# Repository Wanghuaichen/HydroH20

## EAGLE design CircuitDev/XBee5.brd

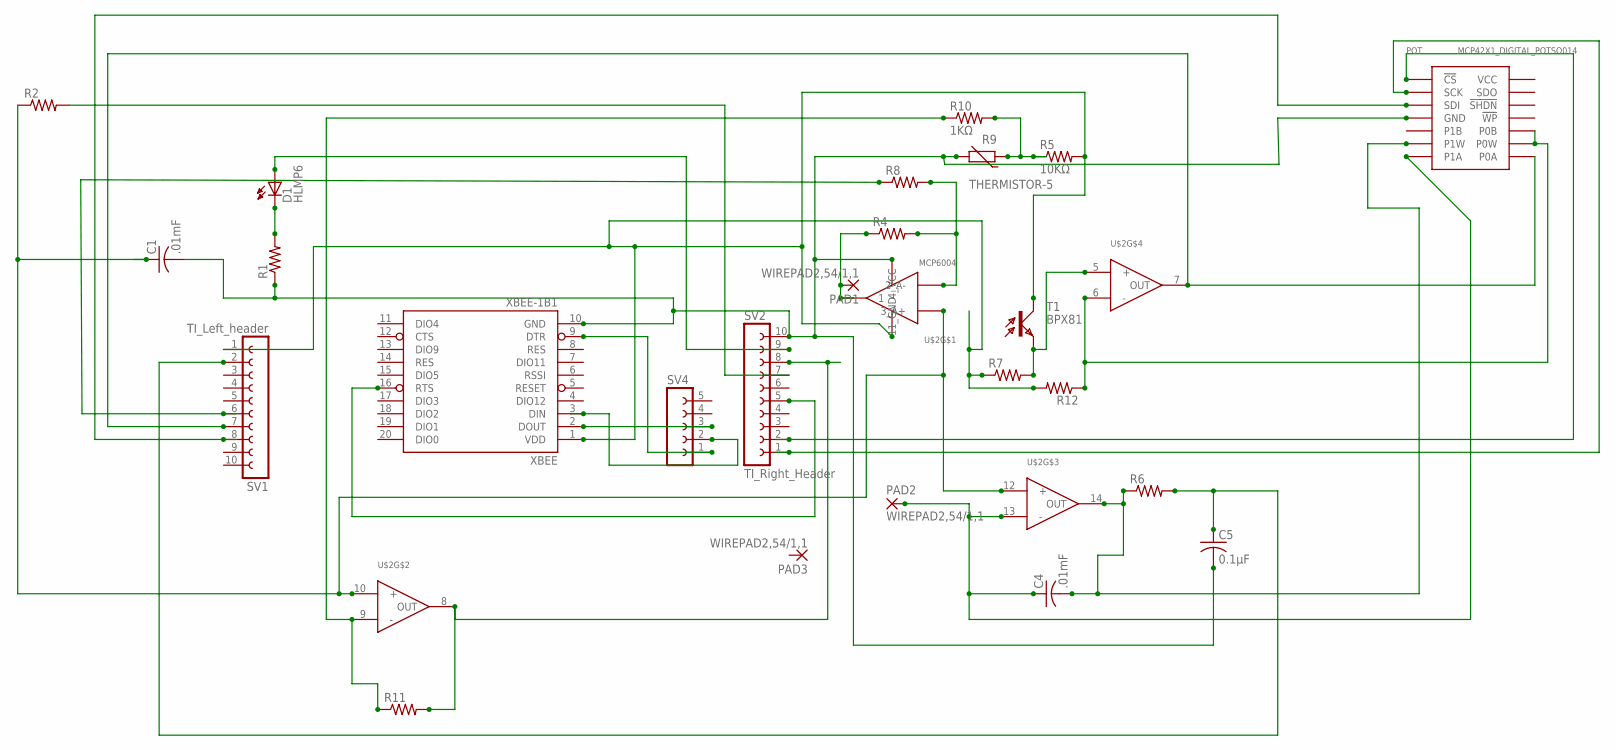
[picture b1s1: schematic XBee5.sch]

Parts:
C1, C4: .01mF; C0603
C5: 0.1μF; C0603
D1: HLMP6
PAD1, PAD2, PAD3: WIREPAD2,54/1,1; 2,54/1,1
POT: MCP42X1_DIGITAL_POTSO014; SO014
R1, R2, R4, R6, R7, R8, R11, R12: R-US_R0603; R0603
R5: 10KΩ; R0603
R9: THERMISTOR-5; R-5
R10: 1KΩ; R0603
SV1: TI_Left_header; FE10
SV2: TI_Right_Header; FE10
SV4: FE05-1
T1: BPX81
U$2: MCP6004; SO014
XBEE: XBEE-1B1; XBEE-1

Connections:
GND: C1.2, C5.2, POT.P4 (GND), R1.1, R9.2, SV2.10, U$2.11 (11_GND), XBEE.10 (GND)
unnamed: D1.K, R1.2
unnamed: R7.2, T1.E, U$2.5 (+)
unnamed: SV4.3, XBEE.2 (DOUT)
unnamed: SV4.1, XBEE.9 (DTR)
unnamed: SV4.2, XBEE.3 (DIN)
unnamed: R2.2, SV2.7
unnamed: POT.P9 (P0W), POT.P10 (P0B), R12.1, U$2.6 (-)
unnamed: R11.2, SV2.8, U$2.8 (OUT)
unnamed: R10.1, R11.1, U$2.9 (-)
unnamed: PAD1.1, R4.1, U$2.1
unnamed: D1.A, SV2.9
unnamed: C4.1, PAD2.1, POT.P7 (P1A), U$2.13 (-)
unnamed: C4.2, POT.P6 (P1W), R6.1, U$2.14 (OUT)
unnamed: C5.1, R6.2, SV1.2
unnamed: R5.1, R9.1, R10.2
unnamed: R4.2, R8.2, U$2.2 (2_A-)
unnamed: SV2.5, XBEE.16 (RTS)
POT_CS: POT.P1 (!CS), SV2.2
POT_SCK: POT.P2 (SCK), SV2.1
POT_SDI: POT.P3 (SDI), SV1.8
PULSE: R8.1, SV1.6
PWM-VCC/2: C1.1, R2.1, U$2.3 (3_A+), U$2.10 (+), U$2.12 (+)
TI_PN7_READ: POT.P8 (P0A), SV1.7, U$2.7 (OUT)
VCC: R5.2, R7.1, R12.2, SV1.1, T1.C, U$2.4 (4_VCC), XBEE.1 (VDD)

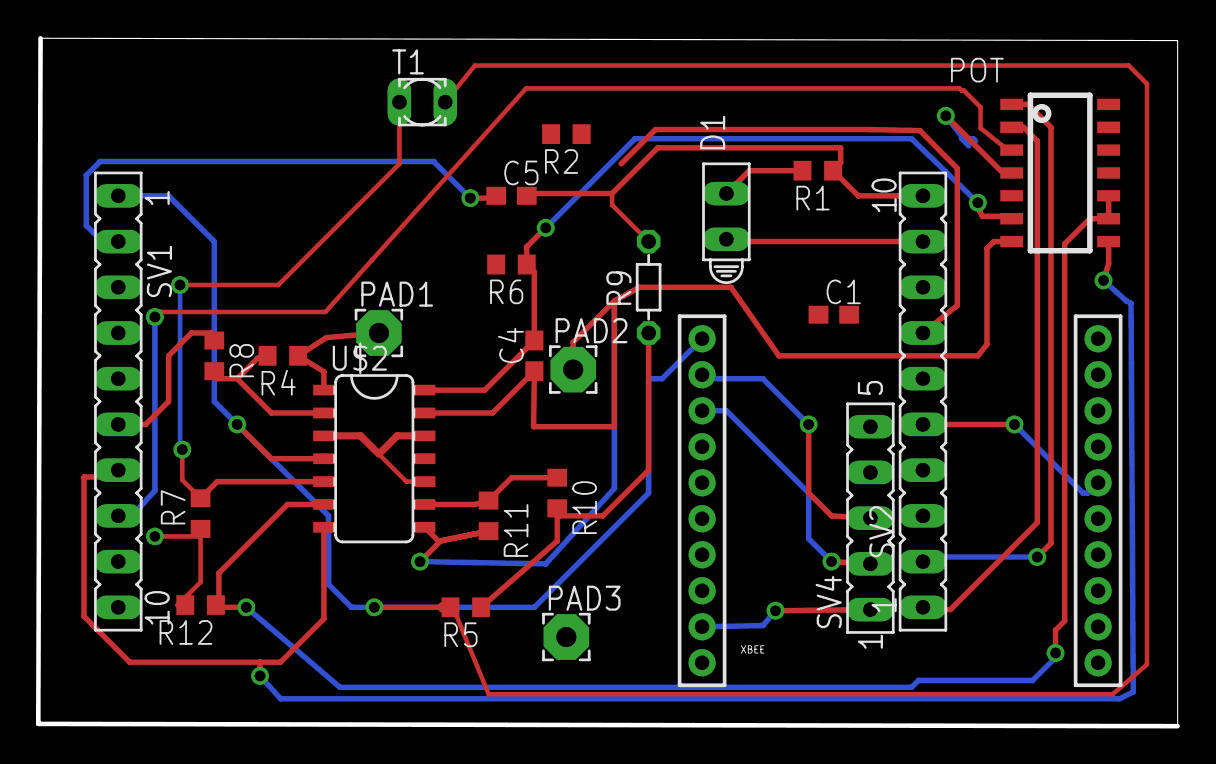
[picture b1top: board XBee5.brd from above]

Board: 2 copper layers, 63.3 x 38.2 mm, 25 parts (0 on the bottom side), 25 nets.

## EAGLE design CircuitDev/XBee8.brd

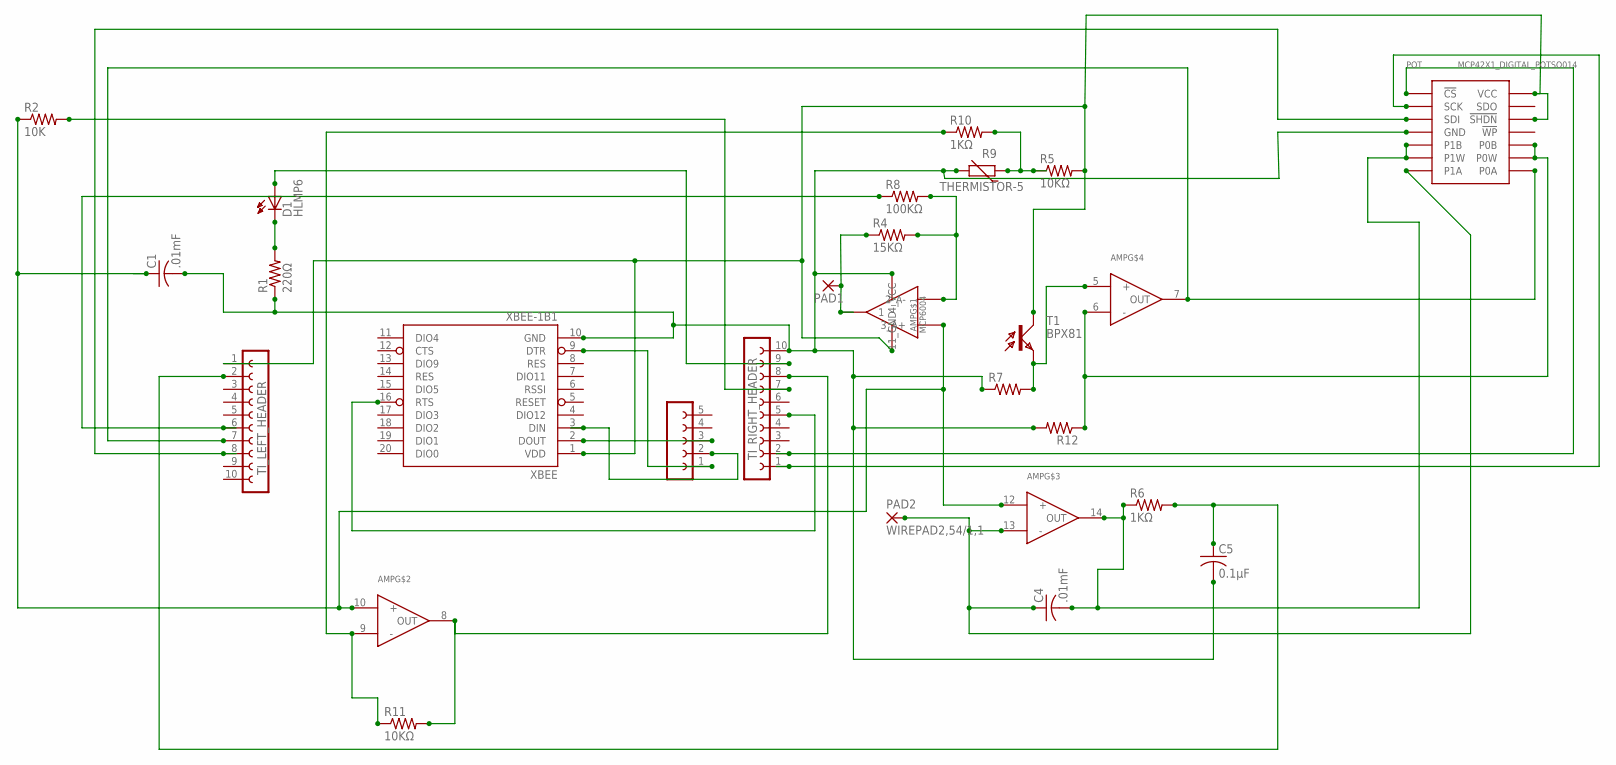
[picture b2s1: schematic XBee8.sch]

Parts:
AMP: MCP6004; SO014
C1, C4: .01mF; C0603
C5: 0.1μF; C0603
D1: HLMP6
PAD1, PAD2: WIREPAD2,54/1,1; 2,54/1,1
POT: MCP42X1_DIGITAL_POTSO014; SO014
R1: 220Ω; R0603
R2: 10K; R0603
R4: 15KΩ; R0603
R5, R11: 10KΩ; R0603
R6, R10: 1KΩ; R0603
R7, R12: R-US_R0603; R0603
R8: 100KΩ; R0603
R9: THERMISTOR-5; R-5
T1: BPX81
TI_LEFT_HEADER: FE10
TI_RIGHT_HEADER: FE10
XBEE: XBEE-1B1; XBEE-1
 : FE05-1

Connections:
GND: AMP.11 (11_GND), C1.2, C5.2, POT.P4 (GND), R1.1, R7.1, R9.2, R12.2, TI_RIGHT_HEADER.10, XBEE.10 (GND)
unnamed: D1.K, R1.2
unnamed: AMP.5 (+), R7.2, T1.E
unnamed: XBEE.2 (DOUT), .3
unnamed: XBEE.9 (DTR), .1
unnamed: XBEE.3 (DIN), .2
unnamed: R2.2, TI_RIGHT_HEADER.7
unnamed: AMP.6 (-), POT.P9 (P0W), POT.P10 (P0B), R12.1
unnamed: AMP.8 (OUT), R11.2, TI_RIGHT_HEADER.8
unnamed: AMP.9 (-), R10.1, R11.1
unnamed: AMP.1, PAD1.1, R4.1
unnamed: D1.A, TI_RIGHT_HEADER.9
unnamed: AMP.13 (-), C4.1, PAD2.1, POT.P7 (P1A)
unnamed: AMP.14 (OUT), C4.2, POT.P5 (P1B), POT.P6 (P1W), R6.1
unnamed: C5.1, R6.2, TI_LEFT_HEADER.2
unnamed: R5.1, R9.1, R10.2
unnamed: AMP.2 (2_A-), R4.2, R8.2
unnamed: TI_RIGHT_HEADER.5, XBEE.16 (RTS)
POT_CS: POT.P1 (!CS), TI_RIGHT_HEADER.2
POT_SCK: POT.P2 (SCK), TI_RIGHT_HEADER.1
POT_SDI: POT.P3 (SDI), TI_LEFT_HEADER.8
PULSE: R8.1, TI_LEFT_HEADER.6
PWM-VCC/2: AMP.3 (3_A+), AMP.10 (+), AMP.12 (+), C1.1, R2.1
TI_PN7_READ: AMP.7 (OUT), POT.P8 (P0A), TI_LEFT_HEADER.7
VCC: AMP.4 (4_VCC), POT.P12 (!SHDN), POT.P14 (VCC), R5.2, T1.C, TI_LEFT_HEADER.1, XBEE.1 (VDD)

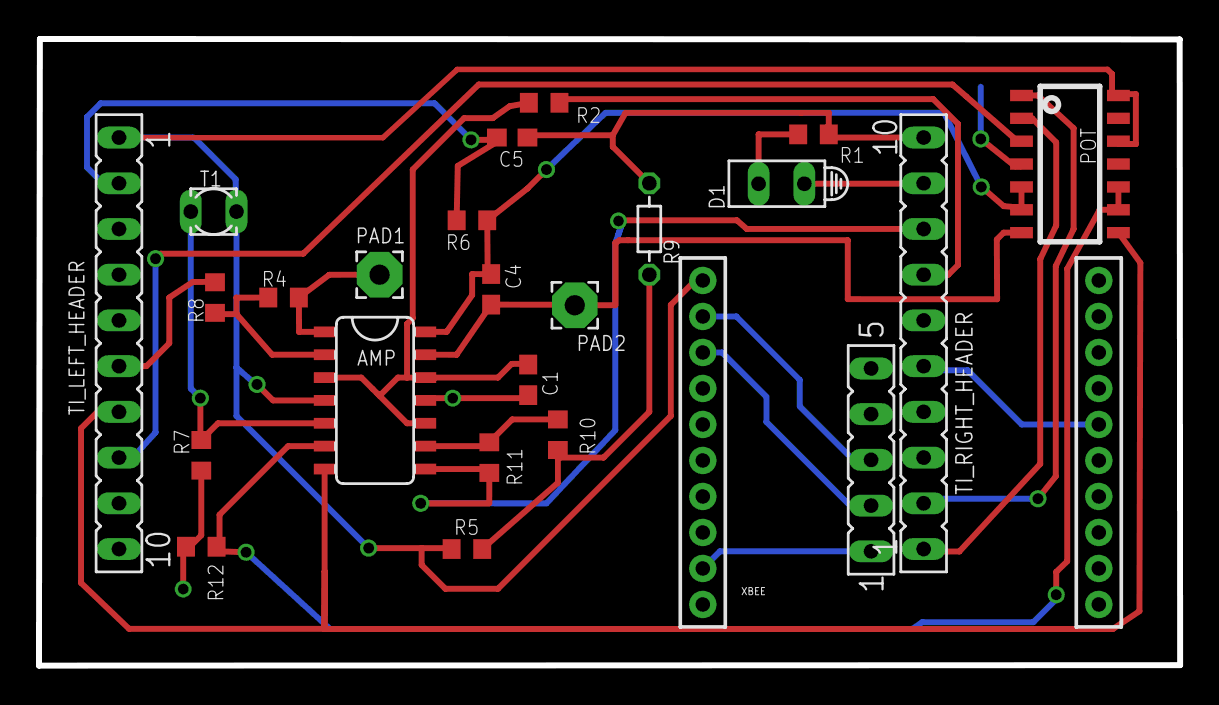
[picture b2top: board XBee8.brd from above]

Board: 2 copper layers, 63.4 x 34.8 mm, 24 parts (0 on the bottom side), 25 nets.

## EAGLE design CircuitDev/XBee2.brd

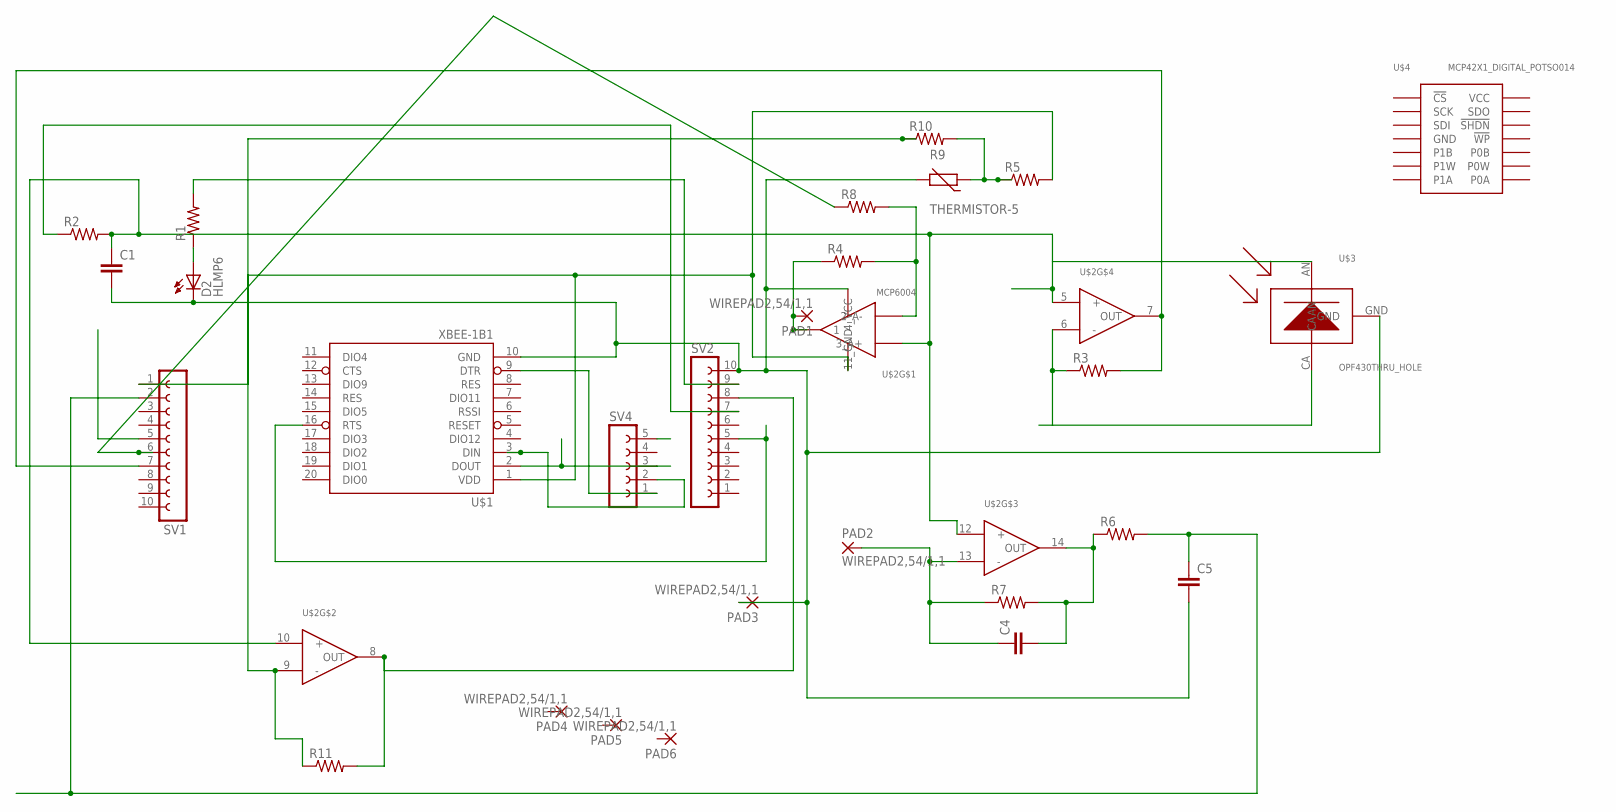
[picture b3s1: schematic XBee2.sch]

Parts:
C1, C4, C5: C-EUC1206; C1206
D2: HLMP6
PAD1, PAD2, PAD3, PAD4, PAD5, PAD6: WIREPAD2,54/1,1; 2,54/1,1
R1, R2, R3, R4, R5, R6, R7, R8, R10, R11: R-US_M1206; M1206
R9: THERMISTOR-5; R-5
SV1, SV2: FE10-1; FE10
SV4: FE05-1
U$1: XBEE-1B1; XBEE-1
U$2: MCP6004; SO014
U$3: OPF430THRU_HOLE; OPF430
U$4: MCP42X1_DIGITAL_POTSO014; SO014

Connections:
GND: C1.2, C5.2, D2.K, PAD3.1, R9.2, SV2.10, U$1.10 (GND), U$2.11 (11_GND), U$3.GND
unnamed: R5.2, SV1.1, U$1.1 (VDD), U$2.4 (4_VCC)
unnamed: R3.1, U$2.6 (-), U$3.CA
unnamed: SV4.3, U$1.2 (DOUT)
unnamed: SV4.1, U$1.9 (DTR)
unnamed: SV4.2, U$1.3 (DIN)
unnamed: C1.1, R2.2, U$2.3 (3_A+), U$2.5 (+), U$2.10 (+), U$2.12 (+), U$3.AN
unnamed: D2.A, R1.1
unnamed: R3.2, SV1.7, U$2.7 (OUT)
unnamed: R2.1, SV2.7
unnamed: R11.2, SV2.8, U$2.8 (OUT)
unnamed: R10.1, R11.1, U$2.9 (-)
unnamed: PAD1.1, R4.1, U$2.1
unnamed: R1.2, SV2.9
unnamed: R8.1, SV1.6
unnamed: C4.1, PAD2.1, R7.1, U$2.13 (-)
unnamed: C4.2, R6.1, R7.2, U$2.14 (OUT)
unnamed: C5.1, R6.2, SV1.2
unnamed: R5.1, R9.1, R10.2
unnamed: R4.2, R8.2, U$2.2 (2_A-)
unnamed: SV2.5, U$1.16 (RTS)

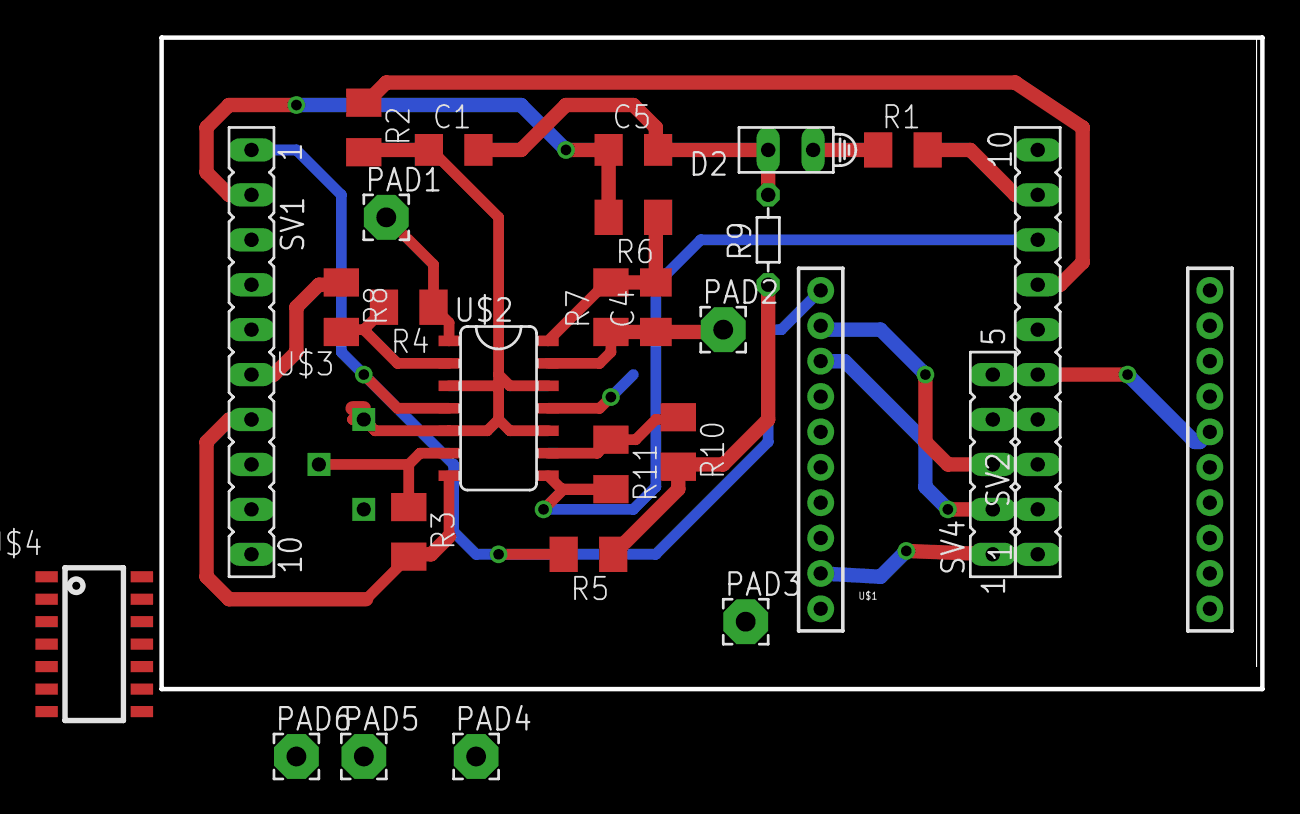
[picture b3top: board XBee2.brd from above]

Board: 2 copper layers, 62.2 x 36.8 mm, 28 parts (0 on the bottom side), 21 nets.

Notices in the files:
parts and their libraries:
SparkFun-RF: Licensing: Creative Commons ShareAlike 4.0 International - https://creativecommons.org/licenses/by-sa/4.0
